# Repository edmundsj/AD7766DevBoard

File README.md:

# AD7766DevBoard
Development Board for AD7766 ADC

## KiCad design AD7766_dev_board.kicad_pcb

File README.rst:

AD7766DevBoard
================
Getting Started
-----------------
- Apply 7.5V to the "7.5V" pin, and gruond to the "GND" pin.

.. csv-table::
    :widths: 25 25 25 25 25
    :file: bom.csv

Debugging
-----------
- Make sure the data ready pin in the Teensy software corresponds to the pin (the layout changed from the Dev Borad)

Issues in Version 1
---------------------
- [FIXED v2] Added drill holes for standoffs 
- [FIXED v2] Selected diode package is not 0805, it's much too large
- [FIXED v2] Hand soldering of filters is very difficult, the out-going pads should be made larger.
- [FIXED v2] The TRIM pin should not be connected to ground, it shouldn't be connected to anything.
- [FIXED v2] a 100nF capacitor at the output of the voltage reference is more than sufficient for noise performance, it adds only 200nV of noise per sample. Remove the 10uF capacitor.
- [FIXED v2] R1 and R2 were switched - they should have the opposite values.
- [FIXED v2] The teensy socket does not actually fit standard header pins - the holes are too small. Need to swap out this part.
- [FIXED v2] Should add pin names for the other output headers.
- [FIXED v2] Removed "U1" and "U2" text
 
Issues in Version 2
---------------------

- [FIXED v3] The MCLK output is 3.3V, and the AD7766 is expecting 2.5V. Added a voltage divider. The datasheet says it's within the absolute maximum ratings, though, so it should work.
- [FIXED v3] The SYNC/PD pin is also 3.3V but the ADC is expecting 2.5V. 

Appendix 1 - Notes
--------------------
- Currently it looks like everything on the PCB is working except the ADC is not sending any data. The DRDY pin is oscillating at 125kHz, the MCLK and SCLK both look as expected, the power supplies are all correct, and yet the ADC is just sending all zeros to the Teensy. Very odd. I will ask the Analog Devices people potentially what's going on with the ADC, and try to fix this.
- They got back to me and asked if I have a 10uF cap between VREF+ and REFGND, which I currently do not.
- I tried adding both a 10uF cap and a 100uF cap, neither of which fixed the issue. However, now it looks like the SPI clock is not doing anything. I thought I checked it before, but perhaps I did not. It's completely silent, and would explain the zero-bytes back. Ah, well duh, of course it's not going off, my Teensy is waiting for the PC to tell it to start sampling, so I wouldn't expect the SPI clock to be going off. I also don't have the cable I need to tell the Teensy to take some data, so that will have to wait until tomorrow.

Debugging Part 2
__________________
- Man, it would be nice to have some test points I can hook the scope probe into for the SPI channel since it's not working. Also, where is the software? I can't find it on this page, and it should be here. It was pretty easy to find in my 'Software' directory.
- God I think OS 11 fucked everything. It looks like comports which I was using to find available ports doesn't work anymore.
- Fixed the issue by updating pyserial using `pip install pyserial --upgrade`. This was in fact a backwards incompatibility introduced by OS X. Now code appears to be running just fine, but still not getting any valid data from the ADC. Checking serial clock now.
- SPI clock looks good, it's applied in bursts of 3 at a period of 125kHz with a clock period of about 10MHz. Maybe check the other voltages during the sampling? See if VDRIVE or VREF falls?
- Interestingly, the supply is using less current than I would expect.
- With the old PCB (AD7766 dev board) connected and the TIA disconnected, looks like the high-frequency PSD is 82nV/rtHz. Looks like two unit tests failed. No signal from the optical chopper was measured. I also didn't measure anything out of the motor, probably because it's not connected :p. There appears to be lots of low-frequency (60Hz) noise with extra harmonics, which is going to be a serious problem if what I want to measure is a response to 60Hz excitation.
- The high-frequency noise PSD is about 82nV/rtHz with the TIA disconnected, 
- The teensy seems reliable as hell. It's been months and the code still works after multiple restarts. Good work.
- There seems like a bunch of either 1/f noise or some 60Hz nonsense. This seemed to go down once the TIA got powered. When powered on, the TIA has a noise of 320nV/rtHz with a 1MOhm resistor. The expected noise is 260nV/rtHz. There is a significant interferer at ~50kHz I think I've seen before.
- Getting a wrong number of bytes error from the Teensy after plugging in the optical chopper. Now it looks like my unit tests aren't even running, and my code for the Teensy is no longer compiling. Getting two fails (one expected failure, one unexpected) and two errors, both unexpected.
- testMeasureSynchronizationData and testMeasureSynchronizationPoints are both failing even though the optical chopper is on. It looks like the Teensy is somehow getting stuck, and now I have to fucking figure out how my code got corrupted. It looks like the SCPIParser library I was using has been removed from the OS, or at least the OS can't find it anymore.
- I checked the chopper voltage and it all looks fine. A 3.2V square wave at 1kHz. Now a lot of my unit tests are failing. I'm no longer getting any data from the teensy after re-uploading code. This is fucking ridiculous, this is the downside of using multi-platform and multi-language non-standard interfaces. I appear to have successfully broken everything. After restarting the Teensy everything is still broken. Fucking hell, what on earth is going on now?
- Apparently the issue is with my Measure() function. The Teensy is not returning any data. I am only receiving back a single byte from the measured data. If it is the '#' character, then it means my Teensy is just not recording anything from the ADC. The ADC is in fact raising DRDY at 125kHz, so it doesn't appear to be an ADC problem. The device is responding to basic commands, such as identifying itself, so it's not a strictly software problem. I suspect the problem is in the Arduino code. I did not realize upgrading my OS would cause so much chaos.
- It appears the Sample() function is never getting executed, which means that an interrupt is never getting triggered or is never being attached properly. The signal IS pulsing at pin 21 of the Teensy, so this tells me the interrupt is never getting attached. Looks like my code is using the wrong data ready pin.
- Found the issue. The pins are different between the new dev board and the old PCB, my newly-written code was using the wrong pins for the old dev board, but the teensy was initially running the old code. Now I'm only getting 2 bytes back from a measurement.
- Now, after the code was fixed I am failing 4 tests and getting errors on an additional three. Looks like all hell has broken loose. The ADC is also measuring an implausibly large amount of noise, which tells me I might have screwed up the byte order that I am sending or reading stuff in. It's railing things out. However, it does look like the raw data is consistent with this, it's also all over the place. After resetting the device there's still a huge number of bytes in the buffer. I think the device is still sending data even though it should not be sending data. Bytes are accumulating in the buffer after the Measure() command is executed. I don't know why. This should also not be happening. Ah, I accidentally added an extra line. Now the PSD is back to what it was before, the ADC is still working. Now some more of my tests are failing. The PSD is 320nV/rtHz.
- I figured out at least part of the synchronization issue - was using the wrong pin. However, now my unit tests are throwing errors that they weren't before. testMeasureLargeByteCount isn't working. I suspect this has something to do with the failure of the synchronization tests. 
- For some reason on a long measurement, the device stops sending back data after 648533 measurements are taken. This seems suspiciously close to the max value for a 16-bit integer. However, it's declared in the Arduino as a 32-bit signed integer. After it fails to give back the rest of the data, it subsequently fails to communicate at all - it cannot identify itself or do anything. Performing a reset doesn't appear to do anything, which means the device must be stuck somewhere. DataPointsToSample is also an integer. Our device isn't even listening for our commands any more, and it's not sending us any data either. This is very odd. Code also isn't able to upload to the device, so it's being rendered unresponsive for some undetermined reason.
- The device does understand that it needs to read 1 million samples, so it's not an issue of the variable not being set appropriately.
- The device is sending back 1,943,551 bytes of data befor it fails and is subsequently unable to communicate. The second time I tried this it sent back 1,943,551 bytes of data. The failure is consistent and not stoichaistic. For some reason after it sends that number of bytes it just gives up.
- On the arduino sketch it fails at 648157. Second time 648157. It actually prints the next 3 characters "648" on the next line, and says "Done!" after 648157. This behavior is damn consistent. It is able to execute 500,000 measurements multiple times without any issue. I suspect the origin of this error is pretty damn obscure and hard to track down. For now, I'm just going to limit us to 500K measurements. If we want more than 500K, I'm going to need to implement a software fix to query for multiple blocks of 500K. All tests now passing.

New PCB
_________
- The new PCB has the same exact issues as the old one. This tells me there's something wrong with my connections or something. Time to debug the damn thing.
- Just as before, all the voltages seem correct and SCK is pulsing appropriately. The SPI clock frequency is 3MHz.
- Here is a potential issue - the MCLK signal needs to be voltage-divided before it gets to the AD7766, but it appears that it is not being voltage divided. It's not clear how it's getting to the ADC at all.
- I tried applying a 2.5V signal to the ADC MCLK pin. This did not appear to help anything. It's possible that the 3.3V MCLK signal fried some of the sampling circuitry while leaving the SPI circuitry and the DRDY circuitry intact. Implausible, but possible. In this case, I will either need to add the voltage divider at the output (requiring a new PCB revision) or add an on-board frequency synthesizer, like a crystal. I can try populating yet another PCB, but add a resistive divider at the output before I test it. A manual way to reset the ADC also might not be a bad idea. 
- I think The SYNC/PD pin is also 3.3V when it should be 2.5V and needs to be divided down to 2.5V. This is another potential problem. The AD7766 dev board applies a 2.5V signal independent of VDrive.
- Perhaps the teensy is driving the MISO pin? This is not likely, as it's not driving it on the ADC dev board. On the dev board, the MOSI pin isn't connected at all.
- Maybe there are safety features to prevent frying the ADC on the dev board? I should check.
- I have no fucking idea how to increase the sourceMeter compliance from 105uA. I did it before, but I can't seem to be able to do it again.
- The noise from the single-ended board is actually not much better with the keithley than the Tekpower source. I NEED to get my new PCB working so that everything can be on the same PCB and I don't have to deal with the pickup of these wires.

TO TEST:
_________
- Make sure the MISO pin isn't being unintentionally driven by the ADC. Try cutting the trace on the PCB or setting the pinMode to input.

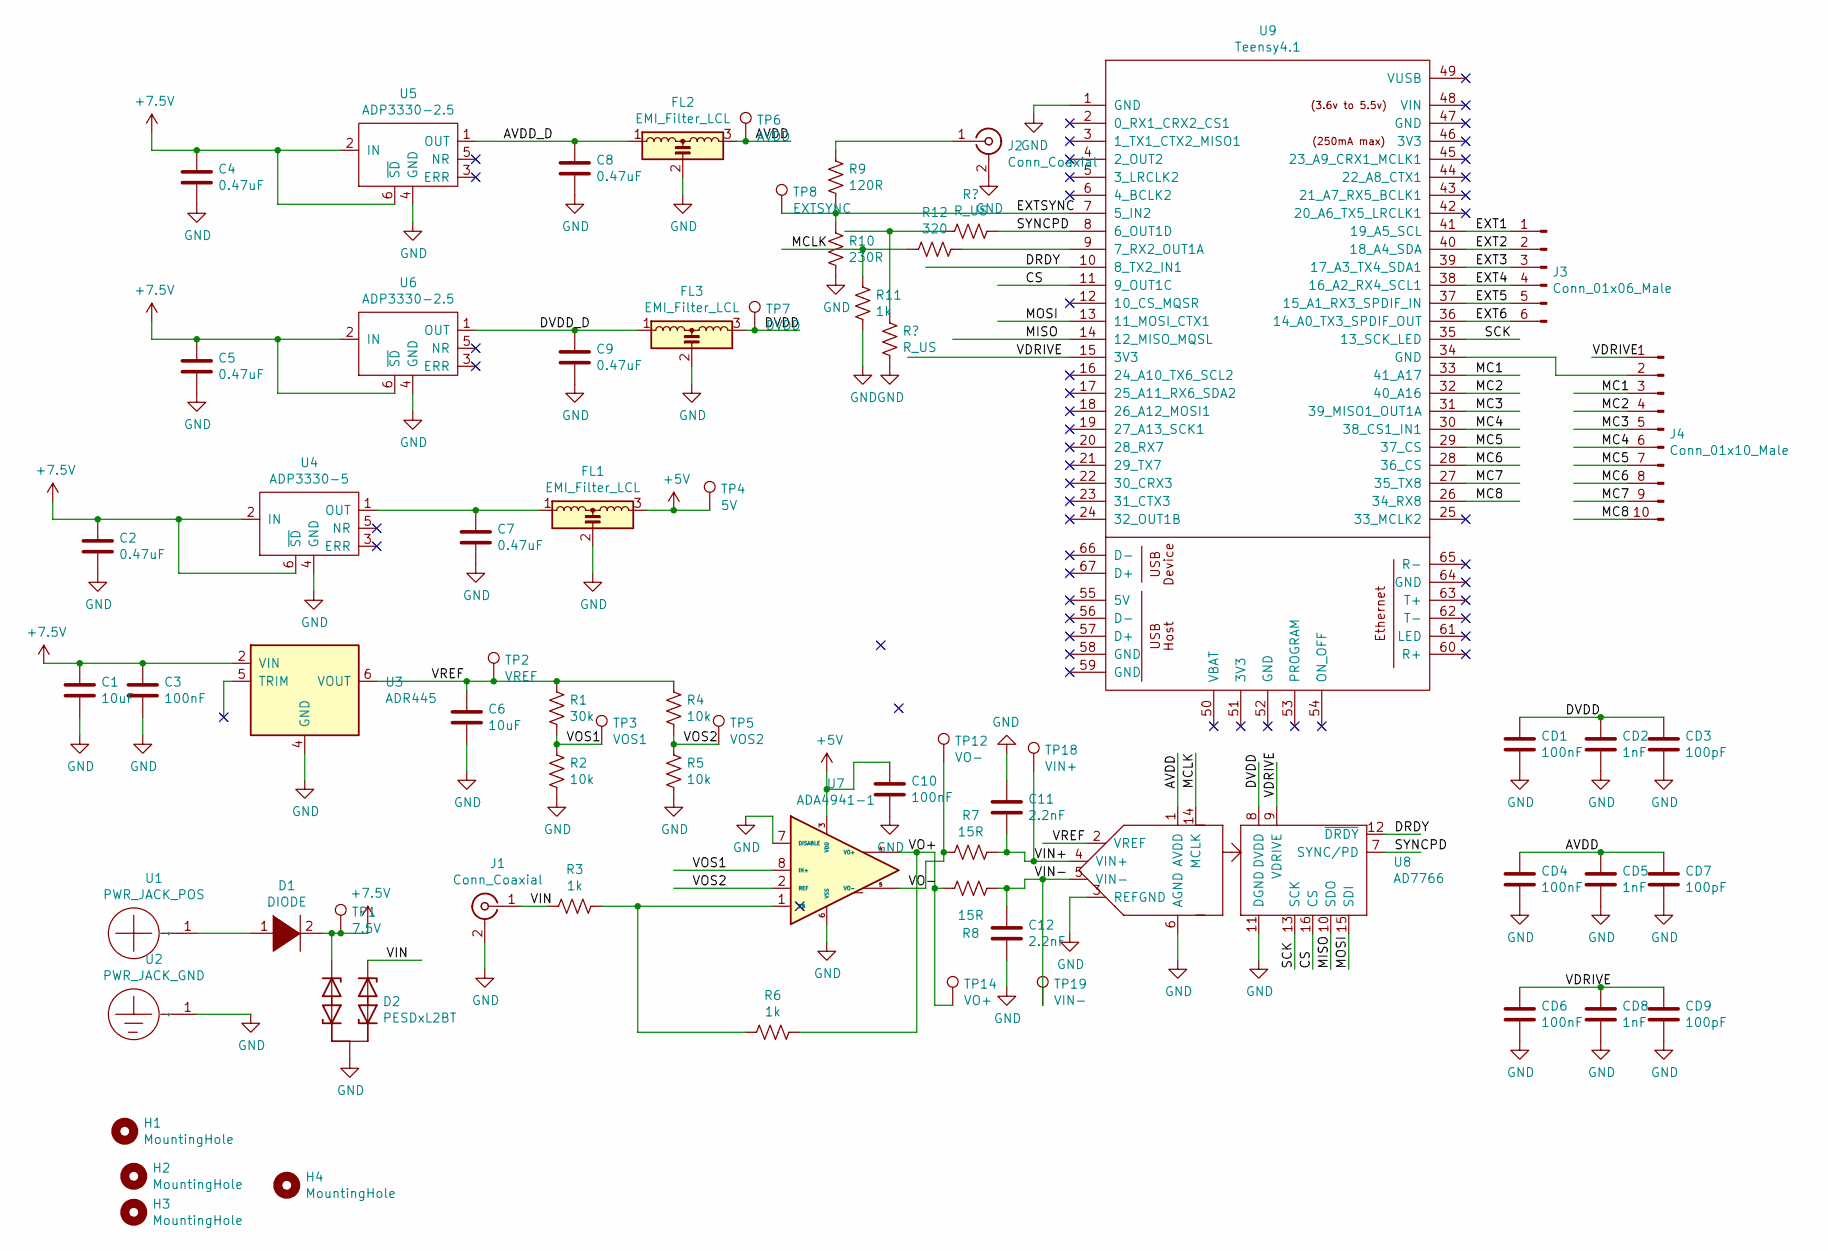
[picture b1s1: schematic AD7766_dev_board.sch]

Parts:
C1: 10uF; C_0805_2012Metric_Pad1.15x1.40mm_HandSolder; Manufacturer Part # GRM21BR6YA106ME43L
C2, C4, C5, C7, C8, C9: 0.47uF; C_0805_2012Metric_Pad1.15x1.40mm_HandSolder; Manufacturer Part # 08051C474K4Z2A
C3, C10: 100nF; C_0805_2012Metric_Pad1.15x1.40mm_HandSolder; Manufacturer Part # C0805C104M5RACTU
C6: 10uF; C_0805_2012Metric_Pad1.15x1.40mm_HandSolder; Manufacturer Part # C0805C104M5RACTU
C11, C12: 2.2nF; C_0805_2012Metric_Pad1.15x1.40mm_HandSolder; Manufacturer Part # CL21B222KDCNFNC
CD1, CD4, CD6: 100nF; C_0805_2012Metric_Pad1.15x1.40mm_HandSolder; Manufacturer Part # C0805C104M5RACTU
CD2, CD5, CD8: 1nF; C_0805_2012Metric_Pad1.15x1.40mm_HandSolder; Manufacturer Part # 08055C102KAT2A
CD3, CD7, CD9: 100pF; C_0805_2012Metric_Pad1.15x1.40mm_HandSolder; Manufacturer Part # C0805C101J5GACTU
D1: DIODE; D_SMA-SMB_Universal_Handsoldering; Manufacturer Part # SK220ATR
D2: PESDxL2BT; SC-59_Handsoldering; Manufacturer Part # PESD15VL2BT,215
FL1, FL2, FL3: EMI_Filter_LCL; 0805_3TERM; Manufacturer Part # NFL21SP157X1C3D
H1, H2, H3, H4: MountingHole; m3_mounting_hole
J1: Conn_Coaxial; CON-SMA-EDGE-S
J2: Conn_Coaxial; BNC_JACK_RA
J3: Conn_01x06_Male; PinHeader_1x06_P2.54mm_Vertical
J4: Conn_01x10_Male; PinHeader_1x10_P2.54mm_Vertical
R1: 30k; R_0805_2012Metric_Pad1.15x1.40mm_HandSolder; Manufacturer Part # CRG0805F3K0
R2, R4, R5: 10k; R_0805_2012Metric_Pad1.15x1.40mm_HandSolder; Manufacturer Part # RC0805FR-071KL
R3, R6: 1k; R_0805_2012Metric_Pad1.15x1.40mm_HandSolder; Manufacturer Part # RC0805FR-071KL
R7, R8: 15R; R_0805_2012Metric_Pad1.15x1.40mm_HandSolder; Manufacturer Part # RK73H2ATTD15R0F
R9: 120R; R_0805_2012Metric_Pad1.15x1.40mm_HandSolder; Manufacturer Part # CRGCQ0805F120R
R10: 230R; R_0805_2012Metric_Pad1.15x1.40mm_HandSolder; Manufacturer Part # RR1220P-241-D
R11: 1k; R_0805_2012Metric_Pad1.15x1.40mm_HandSolder
R12: 320; R_0805_2012Metric_Pad1.15x1.40mm_HandSolder
TP1: 7.5V; TestPoint_Keystone_5000-5004_Miniature
TP2: VREF; TestPoint_Keystone_5000-5004_Miniature
TP3: VOS1; TestPoint_Keystone_5000-5004_Miniature
TP4: 5V; TestPoint_Keystone_5000-5004_Miniature
TP5: VOS2; TestPoint_Keystone_5000-5004_Miniature
TP6: AVDD; TestPoint_Keystone_5000-5004_Miniature
TP7: DVDD; TestPoint_Keystone_5000-5004_Miniature
TP8: EXTSYNC; TestPoint_Keystone_5000-5004_Miniature
TP12: VO-; TestPoint_Keystone_5000-5004_Miniature
TP14: VO+; TestPoint_Keystone_5000-5004_Miniature
TP18: VIN+; TestPoint_Keystone_5000-5004_Miniature
TP19: VIN-; TestPoint_Keystone_5000-5004_Miniature
U1: PWR_JACK_POS; Banana_Jack_1Pin
U2: PWR_JACK_GND; Banana_Jack_1Pin
U3: ADR445; SOIC-8-1EP_3.9x4.9mm_P1.27mm_EP2.29x3mm; Manufacturer Part # ADR445ARZ
U4: ADP3330-5; SOT-23-6_Handsoldering; Manufacturer Part # ADP3330ARTZ-5-RL7
U5, U6: ADP3330-2.5; SOT-23-6_Handsoldering; Manufacturer Part # ADP3330ARTZ-2.5-R7
U7: ADA4941-1; SOIC-8-1EP_3.9x4.9mm_P1.27mm_EP2.29x3mm; Manufacturer Part # ADA4941-1YRZ
U8: AD7766; TSSOP-16_4.4x5mm_P0.65mm; Manufacturer Part # AD7766BRUZ
U9: Teensy4.1; Teensy41

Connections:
+5V: C10.1, FL1.3, TP4.1, U7.3 (VDD)
+7.5V: C1.1, C2.1, C3.1, C4.1, C5.1, D1.2 (A), D2.1 (V1), TP1.1, U3.2 (VIN), U4.2 (IN), U4.6 (~SD), U5.2 (IN), U5.6 (~SD), U6.2 (IN), U6.6 (~SD)
/AVDD: CD4.1, CD5.1, CD7.1, FL2.3, TP6.1, U8.1 (AVDD)
/AVDD_D: C8.1, FL2.1, U5.1 (OUT)
/CS: U8.16 (CS), U9.11 (9_OUT1C)
/DRDY: U8.12 (~DRDY), U9.10 (8_TX2_IN1)
/DVDD: CD1.1, CD2.1, CD3.1, FL3.3, TP7.1, U8.8 (DVDD)
/DVDD_D: C9.1, FL3.1, U6.1 (OUT)
/EXT1: J3.1, U9.41 (19_A5_SCL)
/EXT2: J3.2, U9.40 (18_A4_SDA)
/EXT3: J3.3, U9.39 (17_A3_TX4_SDA1)
/EXT4: J3.4, U9.38 (16_A2_RX4_SCL1)
/EXT5: J3.5, U9.37 (15_A1_RX3_SPDIF_IN)
/EXT6: J3.6, U9.36 (14_A0_TX3_SPDIF_OUT)
/EXTSYNC: R9.2, R10.1, TP8.1, U9.7 (5_IN2)
/MC1: J4.3, U9.33 (41_A17)
/MC2: J4.4, U9.32 (40_A16)
/MC3: J4.5, U9.31 (39_MISO1_OUT1A)
/MC4: J4.6, U9.30 (38_CS1_IN1)
/MC5: J4.7, U9.29 (37_CS)
/MC6: J4.8, U9.28 (36_CS)
/MC7: J4.9, U9.27 (35_TX8)
/MC8: J4.10, U9.26 (34_RX8)
/MCLK: R11.2, R12.2, U8.14 (MCLK)
/MISO: U8.10 (SDO), U9.14 (12_MISO_MQSL)
/MOSI: U8.15 (SDI), U9.13 (11_MOSI_CTX1)
/SCK: U8.13 (SCK), U9.35 (13_SCK_LED)
/VDRIVE: CD6.1, CD8.1, CD9.1, J4.1, U8.9 (VDRIVE), U9.15 (3V3)
/VIN: D2.2 (V2), J1.1 (In), R3.2
/VIN+: C11.2, R7.1, TP18.1, U8.4 (VIN+)
/VIN-: C12.1, R8.1, TP19.1, U8.5 (VIN-)
/VO+: R6.1, R8.2, TP14.1, U7.4 (VO+)
/VO-: R7.2, TP12.1, U7.5 (VO-)
/VOS1: R1.2, R2.1, TP3.1, U7.8 (IN+)
/VOS2: R4.2, R5.1, TP5.1, U7.2 (REF)
/VREF: C6.1, R1.1, R4.1, TP2.1, U3.6 (VOUT), U8.2 (VREF)
GND: C1.2, C2.2, C3.2, C4.2, C5.2, C6.2, C7.2, C8.2, C9.2, C10.2, C11.1, C12.2, CD1.2, CD2.2, CD3.2, CD4.2, CD5.2, CD6.2, CD7.2, CD8.2, CD9.2, D2.3 (GND), FL1.2, FL2.2, FL3.2, J1.2 (Ext), J2.2 (Ext), R2.2, R5.2, R10.2, R11.1, U2.1, U3.4 (GND), U4.4 (GND), U5.4 (GND), U6.4 (GND), U7.6 (VSS), U7.7 (DISABLE), U8.3 (REFGND), U8.6 (AGND), U8.11 (DGND), U9.1 (GND); also elsewhere on the board
unnamed: C7.1, FL1.1, U4.1 (OUT)
unnamed: D1.1 (K), U1.1
unnamed: J2.1 (In), R9.1
unnamed: J4.2, U9.34 (GND)
unnamed: R3.1, R6.2, U7.1 (FB)
unnamed: R12.1, U9.9 (7_RX2_OUT1A)

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
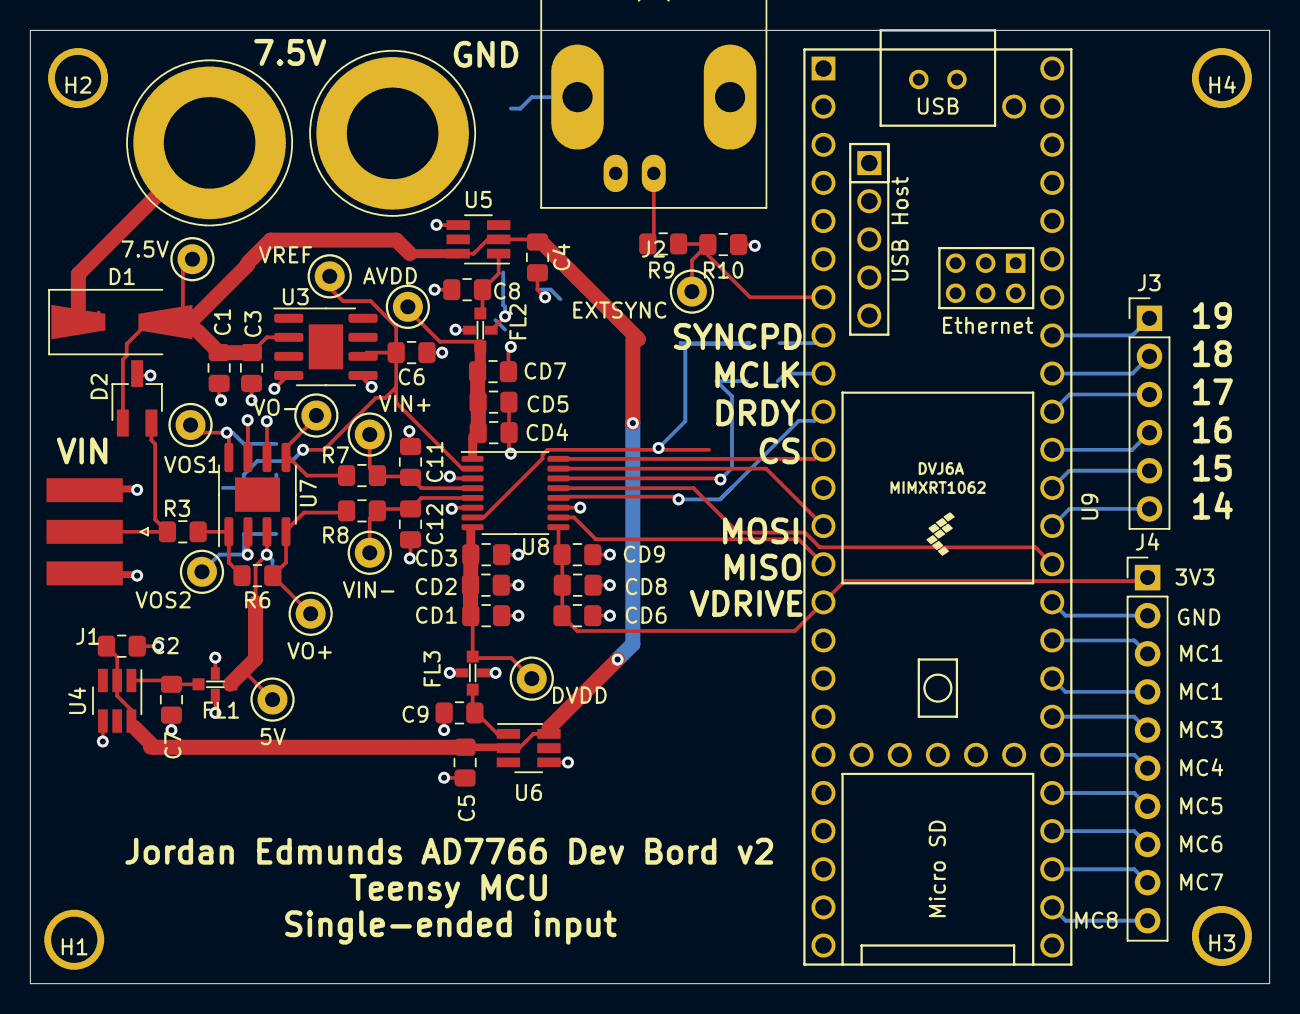
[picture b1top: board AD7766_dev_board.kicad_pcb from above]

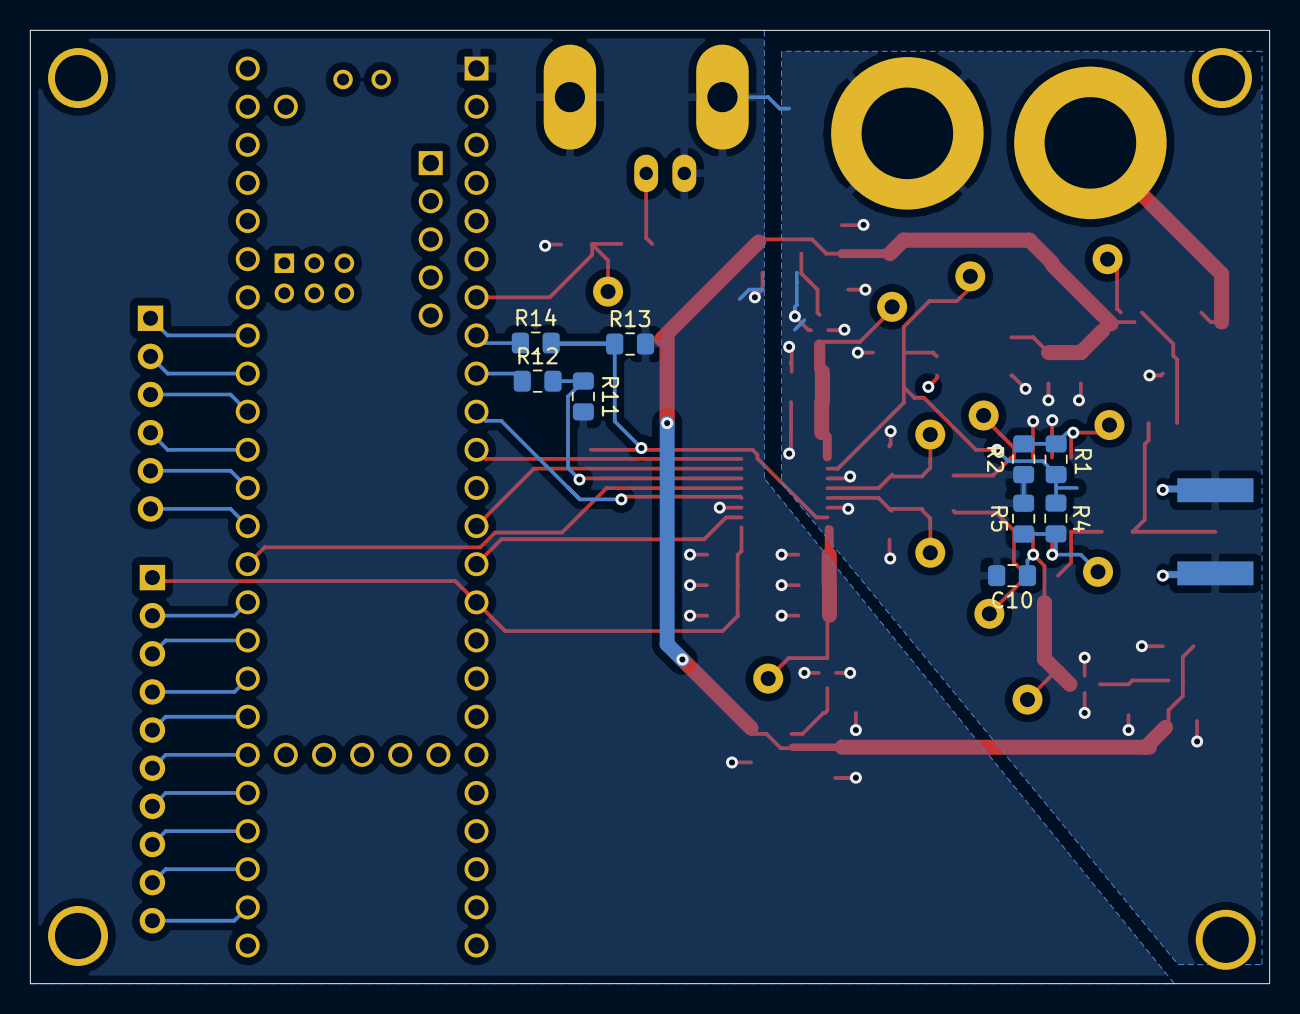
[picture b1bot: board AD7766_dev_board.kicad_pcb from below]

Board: 2 copper layers, 82.5 x 63.5 mm, 69 parts (9 on the bottom side), 45 nets.

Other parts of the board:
R13: 1k; R_0805_2012Metric_Pad1.15x1.40mm_HandSolder
R14: 320R; R_0805_2012Metric_Pad1.15x1.40mm_HandSolder

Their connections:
GND: R13.2; also elsewhere on the board

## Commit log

2020-10-05 added initial version 1.1 of AD7766 development board which has been uploaded to allPCB but not yet purchased
2020-10-10 switched README to reST, added BOM
2020-10-10 attempted to fix README
2020-10-10 revised README, fixed bill of materials
2020-10-21 updated README with current PCB issues
2020-10-21 updated with errors found in version 1, sending out version 2 for fabrication
2020-10-22 added allPCB BOM and position files. Hopefully it works.
2020-10-28 found issue of MCLK not being divided down to 2.5V, but remaining at 3.3V. Fixed issue on PCB, added to README
2020-12-13 fixed readme, schematic
2021-01-13 updated PCB to add voltage divider to SYNC/PD pin
2021-01-19 updated AD7766 dev board schematic, README
